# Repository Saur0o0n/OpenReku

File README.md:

<picture>
  <source media="(prefers-color-scheme: dark)" srcset=".github/images/openreku-logo-white.svg">
  
</picture>

Otwarty projekt sterownika rekuperatora opartego na ESP32 i ESPHome, współpracującego z Home Assistant. Obejmuje elektronikę sterownika oraz konfigurację obsługującą wentylatory, zawory i czujniki.

## Funkcje sterownika

OpenReku steruje wentylacją nawiewno-wywiewną i udostępnia nastawy oraz pomiary w Home Assistant. Regulacja wentylatorów, automatyka bypassu i procedura testowa działają lokalnie w ESPHome. Urządzenie ma też własny panel WWW i obsługuje aktualizacje przez Wi-Fi.

- **Regulacja dwóch wentylatorów** — niezależne ustawianie wydajności nawiewu i wywiewu albo praca zsynchronizowana. Tryb „Moc PWM” ustawia obu wentylatorom jednakowy procent wysterowania. Tryb „Przepływ powietrza” dostosowuje wywiew do zmierzonego przepływu nawiewu, dzięki czemu uwzględnia różnice oporów obu torów powietrza.
- **Korekta bilansu nawiew–wywiew** — w trybie synchronizacji przepływu można ustawić żądaną różnicę w m³/h. Dodatnia korekta oznacza przewagę nawiewu; regulator uzyskuje ją przez zmniejszenie wywiewu rekuperatora. Dołączona automatyzacja Home Assistant zmienia korektę podczas pracy wyciągu kuchennego.
- **Ręczny lub automatyczny bypass** — tryby „Automatyczne grzanie” i „Automatyczne chłodzenie” porównują temperaturę powietrza z czerpni z temperaturą wywiewaną z domu. Bypass otwiera się, gdy powietrze zewnętrzne sprzyja wybranemu celowi, a zamyka, gdy korzystniejszy jest odzysk ciepła lub chłodu. Histereza i czas potwierdzenia warunku ograniczają częste przełączanie.
- **Podgląd parametrów pracy** — temperatury i wilgotności w czterech punktach: czerpni, nawiewie, wywiewie i wyrzutni, a także obroty obu wentylatorów i przepływy powietrza, zależnie od wyposażenia. Zawartość wilgoci jest również obliczana w g/kg suchego powietrza. Karty Home Assistant udostępniają wykresy z zakładkami oraz wyliczaną po stronie HA sprawność temperaturową i odzysk wilgoci.
- **Test do obserwacji zużycia filtrów** — sterownik zamyka bypass, ustawia stałe wysterowanie wentylatorów i po ustabilizowaniu pracy uśrednia przepływ oraz obroty. Wyniki odniesione do nastawy PWM pozwalają porównywać kolejne pomiary; ostatni wynik jest zachowywany po restarcie. Na czas testu blokowane są zmiany nastaw, a po zakończeniu przywracane wcześniejsze ustawienia. Harmonogram zapewnia automatyzacja Home Assistant. Test dostarcza danych do oceny zmian, bez automatycznego alarmu wymiany filtra.

## Opis

Troche więcej o samym powstaniu projektu i co chciałem osiągnąć można przeczytać we [wpisie na mojej stronie](https://adrian.siemieniak.net/portal/sterownik-rekuperatora-cwk-450-o3zone-paruszewski/).

## Wyposażenie opcjonalne

Funkcje można dobrać do wyposażenia rekuperatora:

| Wariant / komponent | Dostępne funkcje |
| --- | --- |
| Dwa wentylatory ze sterowaniem PWM | Podstawowa regulacja niezależna lub wspólne wysterowanie w trybie „Moc PWM”, bez pomiaru przepływu. |
| Sygnały obrotów wentylatorów | Odczyt RPM i pomiary obrotów w procedurze testowej. Nie są wymagane do samego sterowania PWM. |
| Czujniki temperatury i wilgotności SHT4x | Monitoring do czterech torów powietrza. Temperatury czerpni i wywiewu służą automatyce bypassu, a nawiewu i wywiewu — obliczaniu przepływów. |
| Dwie zwężki Venturiego z czujnikami różnicy ciśnień SDP810-125Pa oraz pomiar temperatury nawiewu i wywiewu | Wyliczanie przepływów w m³/h, ich automatyczne bilansowanie i pomiary przepływu w teście filtrów. Obliczenia uwzględniają temperaturę powietrza oraz zadane wymiary zwężek. |
| Siłownik bypassu z osobnymi sygnałami otwierania i zamykania | Ręczne otwieranie i zamykanie, a z pomiarem temperatury czerpni i wywiewu także automatyczne grzanie lub chłodzenie. Czas ruchu jest ustawiany w konfiguracji; stan bypassu wynika z wydanych poleceń, bez pomiaru jego rzeczywistego położenia. |

Zamieszczony YAML odpowiada pełnemu zestawowi w instalacji autora. Warianty uproszczone wymagają dostosowania konfiguracji: usunięcia nieużywanych komponentów i zależnych od nich odczytów lub procedur. Nie ma automatycznego wykrywania wyposażenia ani gotowych profili tych wariantów.

## Zawartość repozytorium

| Katalog | Zawartość |
| --- | --- |
| [PCB/](PCB/) | Projekt płytki w wersji 1.1: schematy i PCB KiCad, lokalne biblioteki, lista elementów BOM, Gerbery do produkcji. |
| [ESPHome/](ESPHome/) | Konfiguracja `rekuperator.yaml` z obsługą urządzenia i integracją z Home Assistant oraz wzór `secrets.yaml.example` do uzupełnienia własnymi danymi dostępowymi. |
| [HomeAssistant/](HomeAssistant/) | Karta sterowania i wykresy Home Assistant, sensory sprawności, automatyzacje testu filtrów i korekty bilansu oraz podkład graficzny karty. |
| [Venturi/](Venturi/) | Model zwężki Venturiego do pomiaru przepływu powietrza: projekt FreeCAD i eksporty STEP obu części. |

Opis plików i instrukcję otwarcia projektu elektroniki zawiera [PCB/README.md](PCB/README.md). Przygotowanie konfiguracji i pliku sekretów opisano w [ESPHome/README.md](ESPHome/README.md). Sposób dodania karty do panelu opisano w [HomeAssistant/README.md](HomeAssistant/README.md).

## Licencja

Projekty PCB i mechaniki, dokumentacja i własne grafiki są udostępnione na licencji [CC BY-NC 4.0](LICENSES/CC-BY-NC-4.0.txt), a kod i konfiguracje YAML ESPHome oraz Home Assistant — na [PolyForm Noncommercial 1.0.0](LICENSES/PolyForm-Noncommercial-1.0.0.txt).

Możesz je kopiować, modyfikować i udostępniać do celów niekomercyjnych, na warunkach odpowiedniej licencji. Przy udostępnianiu zachowaj informację o autorze **Sauron**, nazwie **OpenReku**, [źródle projektu](https://github.com/Saur0o0n/OpenReku) i licencji; dla materiałów CC BY-NC oznacz również wprowadzone zmiany. Kod zawiera obowiązkową informację `Required Notice:`.

Zakres licencji i wyłączenia dotyczące cudzych materiałów określa [LICENSE](LICENSE). Wykorzystanie komercyjne wykraczające poza udzielone licencje wymaga osobnej zgody właścicieli praw.

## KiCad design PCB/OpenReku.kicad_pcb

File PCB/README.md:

# OpenReku — PCB 1.1

Projekt płytki sterownika rekuperatora OpenReku, rewizja **1.1 z 2026-10-01**. Ten katalog zawiera źródła KiCada, lokalne biblioteki, listę elementów i archiwum produkcyjne PCB. Oprogramowanie ESPHome i pozostałe komponenty projektu należą do osobnych katalogów repozytorium.

## Wizualizacja PCB

## Otwieranie projektu

Otwórz [OpenReku.kicad_pro](OpenReku.kicad_pro) w **KiCad 10**. Potrzebne są standardowe biblioteki symboli, footprintów i — do podglądu 3D — modeli KiCad 10.

Zachowaj razem wszystkie pliki z tego katalogu i podkatalog `Rekuperator.pretty`. KiCad odnajduje lokalne biblioteki względem katalogu, w którym znajduje się `OpenReku.kicad_pro`. Dzięki temu projekt można sklonować do dowolnego miejsca na komputerze.

Tabele `fp-lib-table` i `sym-lib-table` korzystają ze zmiennej `${KIPRJMOD}`, którą KiCad rozwija do katalogu projektu.

Lokalne biblioteki mają nazwę `Rekuperator`, używaną w odwołaniach schematu i PCB.

## Zawartość katalogu

| Plik lub katalog | Typ i przeznaczenie |
| --- | --- |
| [OpenReku.kicad_pro](OpenReku.kicad_pro) | Projekt KiCad: wspólne ustawienia schematu i PCB, klasy sieci oraz konfiguracja kontroli projektu. Główny plik do otwarcia. |
| [OpenReku.kicad_sch](OpenReku.kicad_sch) | Główny schemat KiCad: mikrokontroler, zasilanie części logicznej, interfejsy wentylatorów i odwołania do arkuszy podrzędnych. |
| [I2C.kicad_sch](I2C.kicad_sch) | Podrzędny arkusz schematu: multiplekser I²C i złącza czujników. Otwieraj w kontekście głównego projektu. |
| [230V.kicad_sch](230V.kicad_sch) | Podrzędny arkusz schematu: zasilanie sieciowe, zabezpieczenia, przekaźniki i wyjścia 230 V. |
| [OpenReku.kicad_pcb](OpenReku.kicad_pcb) | Projekt PCB KiCad: obrys płytki, rozmieszczenie elementów, ścieżki, przelotki, wylewki miedzi i nadruki. |
| [OpenReku.kicad_dru](OpenReku.kicad_dru) | Własne reguły DRC KiCada, w tym wymagane odstępy między częścią sieciową i niskonapięciową. |
| [Rekuperator.kicad_sym](Rekuperator.kicad_sym) | Lokalna biblioteka symboli schematowych KiCad; zawiera symbol przekaźnika SSR G3MB-202P. |
| [sym-lib-table](sym-lib-table) | Tabela bibliotek symboli projektu: rejestruje lokalną bibliotekę `Rekuperator.kicad_sym`. |
| [Rekuperator.pretty/](Rekuperator.pretty/) | Lokalna biblioteka footprintów KiCad. Każdy plik `.kicad_mod` opisuje pola lutownicze, obrysy lub grafikę jednego footprintu. Szczegóły poniżej. |
| [fp-lib-table](fp-lib-table) | Tabela bibliotek footprintów projektu: rejestruje katalog `Rekuperator.pretty`. |
| [BOM.csv](BOM.csv) | Lista elementów wersji 1.1, wyeksportowana z całej hierarchii schematu. Format CSV UTF-8, separator przecinek. |
| [OpenReku-v1.1-Gerber.zip](OpenReku-v1.1-Gerber.zip) | Archiwum do wykonania samej PCB: Gerbery obu warstw miedzi, obu soldermasek, górnego nadruku i obrysu, wiercenia PTH/NPTH oraz opis zadania `.gbrjob`. Nie zawiera plików automatycznego montażu. |

### Lokalna biblioteka footprintów

Poniższe pliki znajdują się w `Rekuperator.pretty/`:

| Plik `.kicad_mod` | Przeznaczenie |
| --- | --- |
| `ESP32-WROOM-32U_0.3mm_ThermalDrills.kicad_mod` | Footprint modułu ESP32-WROOM-32U z otworami termicznymi 0,3 mm. |
| `KLS2-EDV-5.08-04P-4_Vertical.kicad_mod` | Czteropinowe złącze interfejsu wentylatora, raster 5,08 mm. |
| `Omron_G3MB-202P_SIP4.kicad_mod` | Footprint przekaźnika SSR Omron G3MB-202P. |
| `PhoenixContact_MC_1,5_4-G-3.5_1x04_P3.50mm_Horizontal_Edge.kicad_mod` | Kątowe, czteropinowe złącze I²C, raster 3,50 mm, z obrysem dopasowanym do montażu przy krawędzi. |
| `PhoenixContact_MSTBA_2,5_2-G-5,08_1x02_P5.08mm_Horizontal_Edge.kicad_mod` | Kątowe, dwupinowe złącze 230 V, raster 5,08 mm, montowane przy krawędzi. |
| `PhoenixContact_MSTBA_2,5_3-G-5,08_1x03_P5.08mm_Horizontal_Edge.kicad_mod` | Kątowe, trzypinowe złącze 230 V, raster 5,08 mm, montowane przy krawędzi. |
| `Logo_OpenReku_36mm.kicad_mod` | Logo OR + OpenReku o szerokości 36 mm na górnej warstwie nadruku; nie jest elementem do zakupu. |

## BOM — lista elementów

`BOM.csv` zawiera **47 grup i 93 elementy**. Grupowanie uwzględnia wartość, footprint, numer części oraz pozostałe eksportowane właściwości, dzięki czemu elementy z odmiennymi uwagami montażowymi pozostają osobnymi pozycjami.

| Kolumna | Znaczenie |
| --- | --- |
| `Reference` | Oznaczenia elementów na schemacie i PCB, np. `R1,R2`. |
| `Quantity` | Liczba elementów w grupie. |
| `Value` | Wartość lub nazwa elementu ze schematu. |
| `Footprint` | Identyfikator biblioteki i footprintu KiCad. |
| `MPN` | Numer części producenta, jeżeli uzupełniono go w schemacie. |
| `MatingConnector` | Opis współpracującego wtyku; wtyk nie jest dodatkowo doliczony do `Quantity`. |
| `Pinout` | Opis wyprowadzeń zapisany w schemacie. |
| `AssemblyNote` | Uwagi montażowe, w tym warunki pominięcia rezystorów podciągających. |
| `DNP` | Oznaczenie elementu przewidzianego do pominięcia przy montażu, jeżeli ustawiono je w KiCadzie. |
| `Datasheet` | Odnośnik do dokumentacji części zapisany w schemacie. |

Puste pole oznacza brak informacji w schemacie. BOM nie obejmuje otworów montażowych H1–H4 ani logo LOGO1. Jest listą elementów projektu; współpracujące wtyki, przewody i osprzęt mechaniczny należy zestawić osobno.

Aby odtworzyć BOM, uruchom w tym katalogu:

```sh
kicad-cli sch export bom \
  --output BOM.csv \
  --fields 'Reference,QUANTITY,Value,Footprint,MPN,MatingConnector,Pinout,AssemblyNote,DNP,Datasheet' \
  --labels 'Reference,Quantity,Value,Footprint,MPN,MatingConnector,Pinout,AssemblyNote,DNP,Datasheet' \
  --group-by 'Value,Footprint,MPN,MatingConnector,Pinout,AssemblyNote,DNP,Datasheet' \
  --sort-field Reference \
  --ref-range-delimiter '' \
  OpenReku.kicad_sch
```

## Rewizja 1.1 względem 1.0

- Obrys PCB zmniejszono z 210 × 180 mm do **170 × 150 mm**.
- Rezystory R1–R41 i kondensatory ceramiczne C1/C3/C4/C5/C6/C7/C8 mają obudowy **1206**. C2 pozostaje tantalowy, a C9 przewlekany.
- Złącza I²C J4–J11 przesunięto o 2 mm w stronę krawędzi, zachowując raster 3,50 mm.
- Złącza 230 V J12–J17 zmieniono z rastra 7,62 mm na **5,08 mm**.
- Przeniesiono C5 i zarezerwowano miejsce dla dłuższego modułu ESP-32S 18 × 25,5 mm. Projekt elektryczny nadal wskazuje ESP32-WROOM-32U; zgodność innego modułu wymaga sprawdzenia jego padów i sposobu podłączenia anteny.
- Zmieniono rozmieszczenie i routing oraz dodano logo OR + OpenReku na górnym nadruku.

Źródła i Gerbery wersji **1.0** są dostępne w historii Git, w commicie `764cad7`. Bieżący katalog zawiera rewizję **1.1**.

## Produkcja PCB

Pliki do wykonania płytki znajdują się w [OpenReku-v1.1-Gerber.zip](OpenReku-v1.1-Gerber.zip). Parametry zamówienia:

- wymiary: **170 × 150 mm**;
- **2 warstwy**, laminat **FR-4 1,6 mm**;
- miedź **35 µm / 1 oz**;
- soldermaska obustronna, nadruk na górze.

Po zmianie projektu PCB należy ponownie wygenerować Gerbery i pliki wierceń.

Reguły DRC określają odstępy 8 mm między częścią sieciową i niskonapięciową oraz 3 mm między różnymi sieciami części sieciowej.

Pliki lokalnych ustawień `*.kicad_prl`, blokady `*.lck`, autosave, kopie zapasowe i cache footprintów są pomijane przez główny [`.gitignore`](../.gitignore). Nie są potrzebne do odtworzenia projektu.

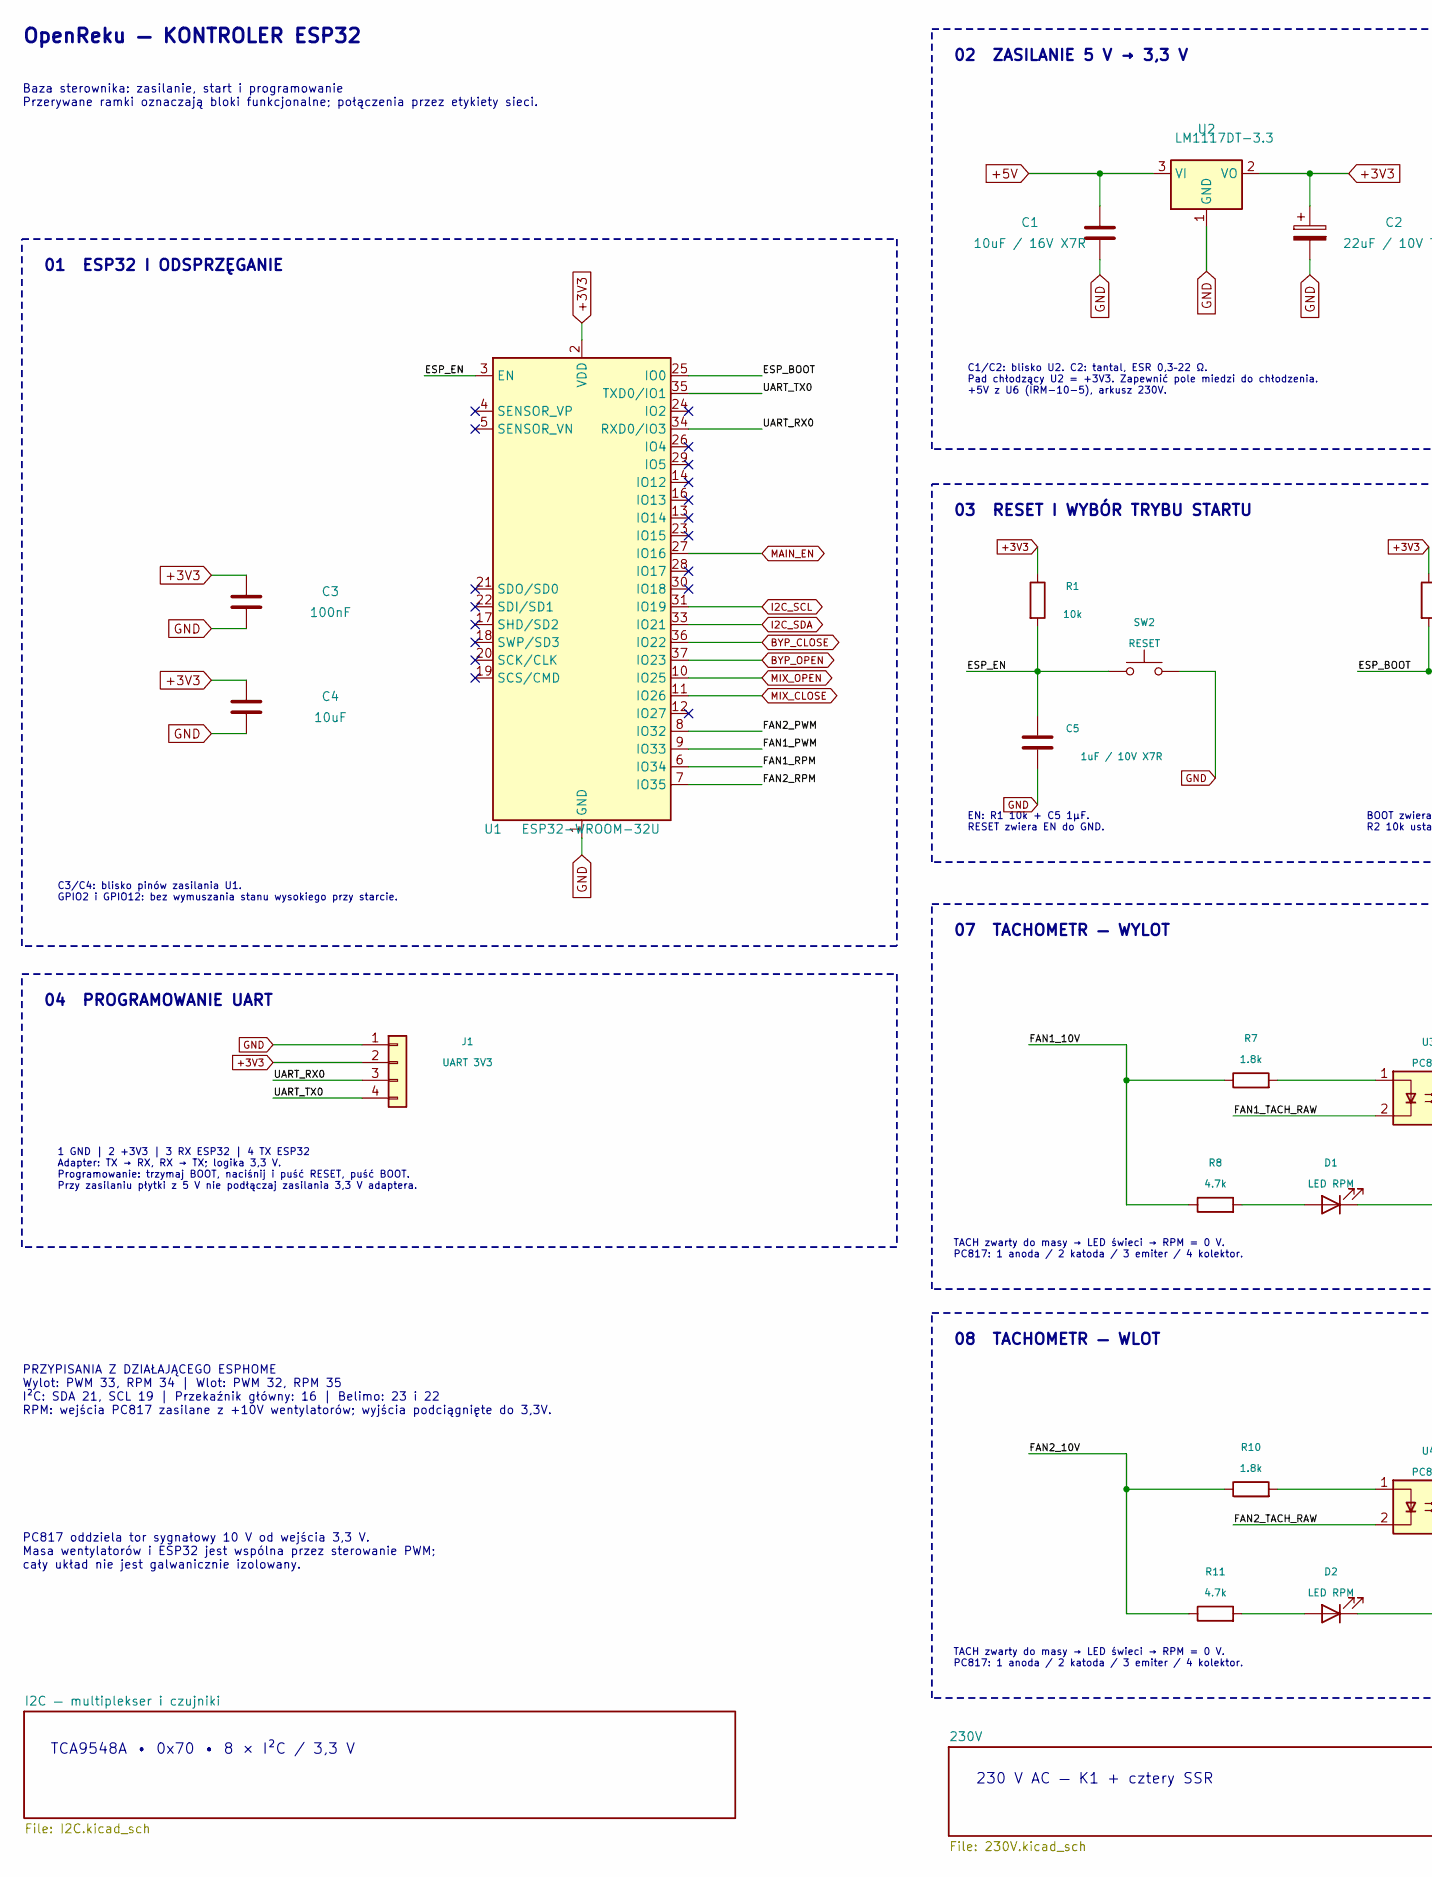
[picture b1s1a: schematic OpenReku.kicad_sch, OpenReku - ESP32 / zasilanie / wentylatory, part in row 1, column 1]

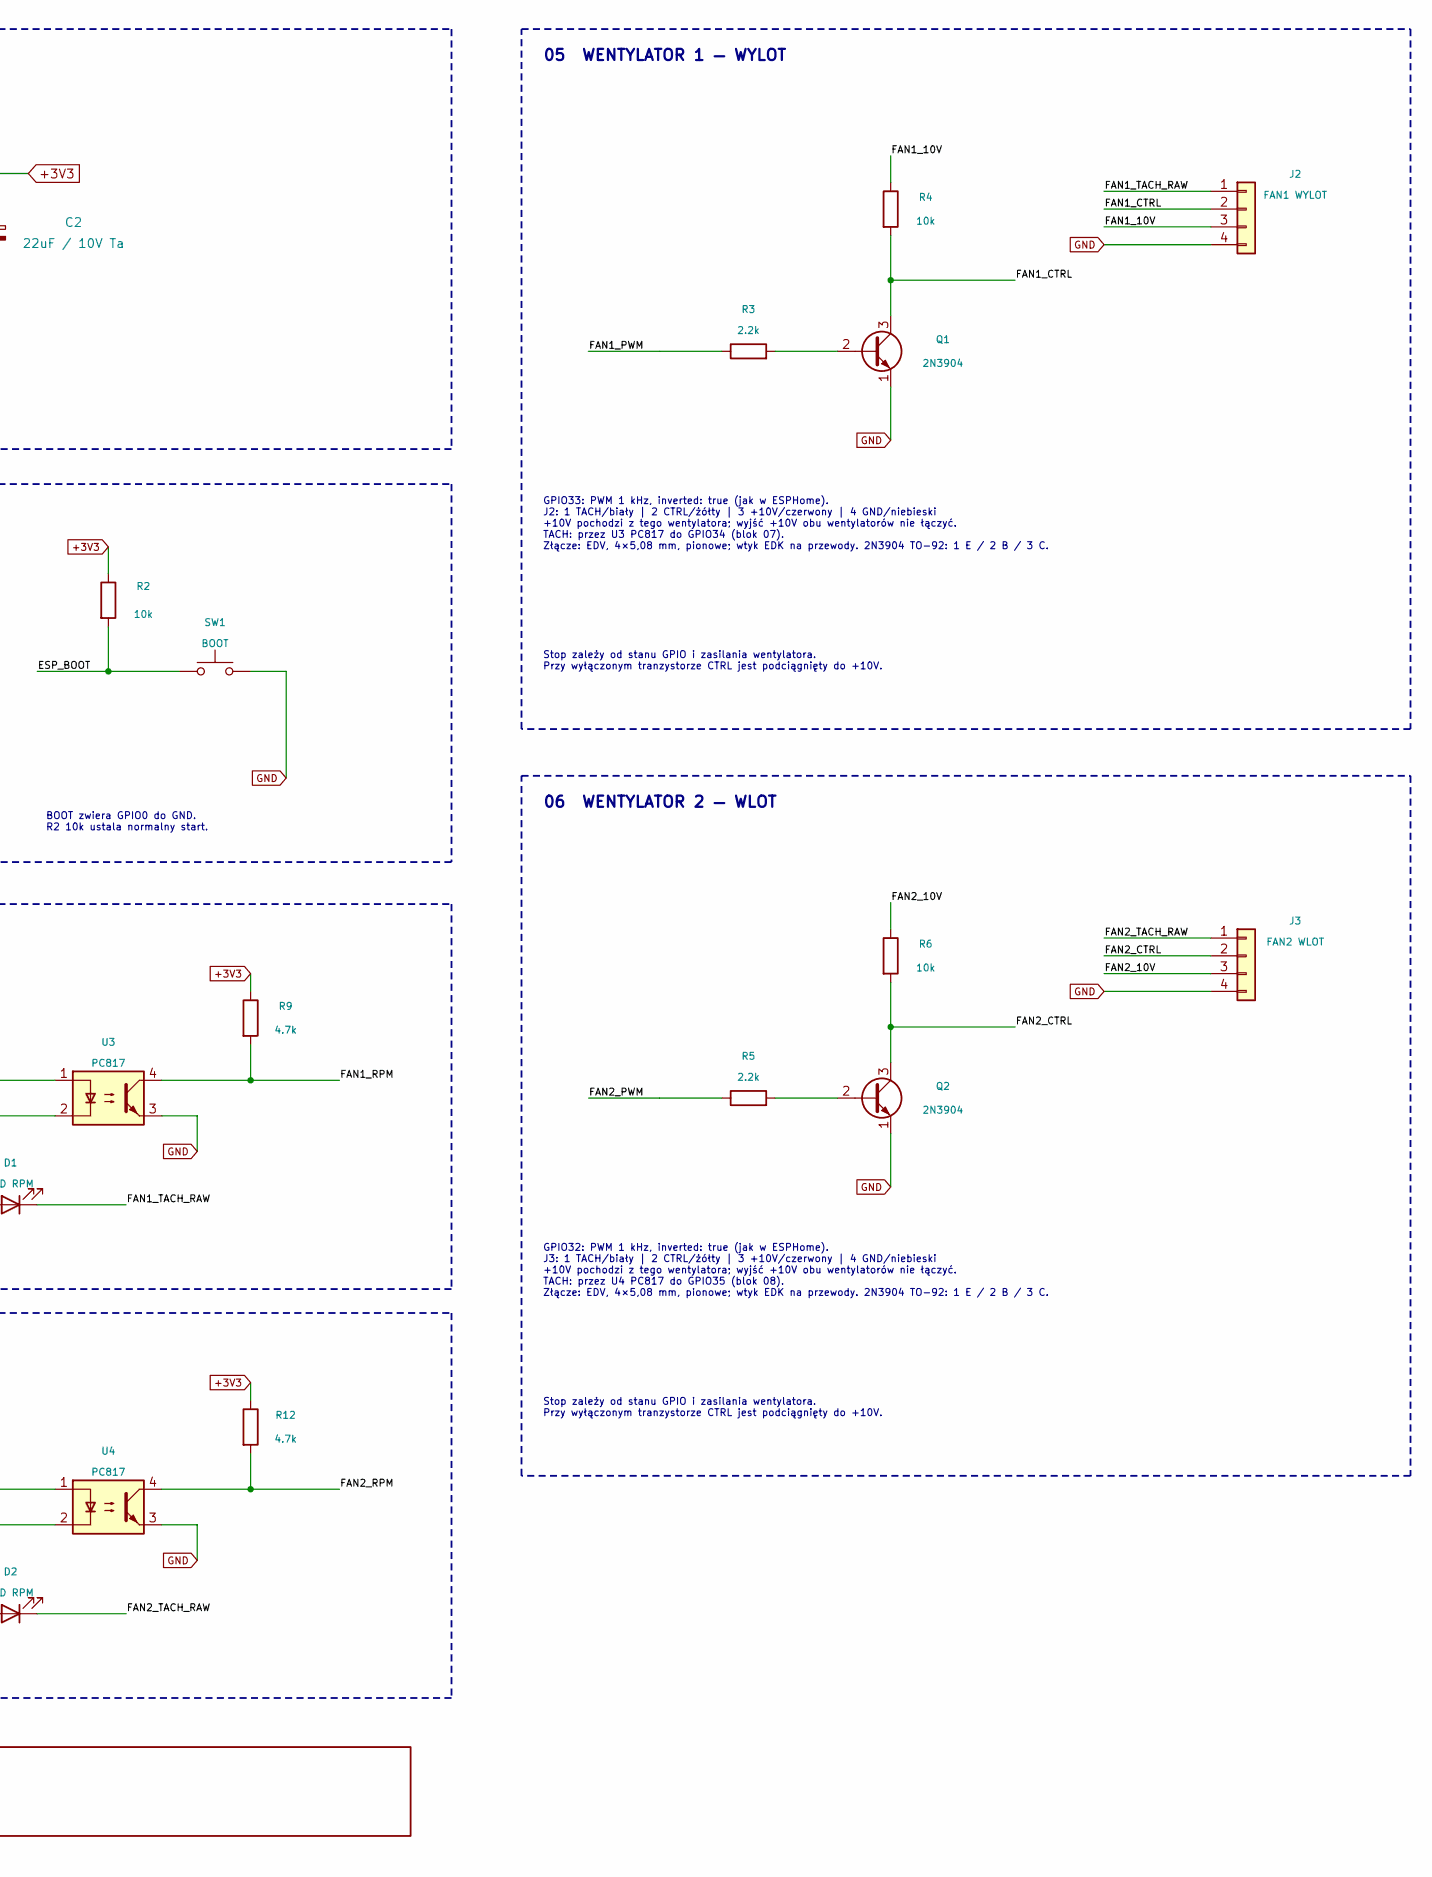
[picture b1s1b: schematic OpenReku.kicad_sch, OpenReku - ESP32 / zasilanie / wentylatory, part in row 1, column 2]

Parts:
C1: 10uF / 16V X7R; C_1206_3216Metric
C2: 22uF / 10V Ta; CP_EIA-3528-21_Kemet-B
C3: 100nF; C_1206_3216Metric
C4: 10uF; C_1206_3216Metric
C5: 1uF / 10V X7R; C_1206_3216Metric
D1, D2: LED RPM; LED_D3.0mm
J1: UART 3V3; PinHeader_1x04_P2.54mm_Vertical
J2: FAN1 WYLOT; KLS2-EDV-5.08-04P-4_Vertical; MPN KLS2-EDV-5.08-04P-4
J3: FAN2 WLOT; KLS2-EDV-5.08-04P-4_Vertical; MPN KLS2-EDV-5.08-04P-4
Q1, Q2: 2N3904; TO-92_Inline
R1, R2, R4, R6: 10k; R_1206_3216Metric
R3, R5: 2.2k; R_1206_3216Metric
R7, R10: 1.8k; R_1206_3216Metric
R8, R9, R11, R12: 4.7k; R_1206_3216Metric
SW1: BOOT; SW_PUSH_6mm
SW2: RESET; SW_PUSH_6mm
U1: ESP32-WROOM-32U; ESP32-WROOM-32U_0.3mm_ThermalDrills
U2: LM1117DT-3.3; TO-252-3_TabPin2
U3, U4: PC817; DIP-4_W7.62mm

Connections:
+3V3: C2.1, C3.1, C4.1, J1.2, R1.1, R2.1, R9.1, R12.1, U1.2 (VDD), U2.2 (VO); also elsewhere on the board
+5V: C1.1, U2.3 (VI); also elsewhere on the board
/ESP_BOOT: R2.2, SW1.1, U1.25 (IO0)
/ESP_EN: C5.1, R1.2, SW2.1, U1.3 (EN)
/FAN1_10V: J2.3, R4.1, R7.1, R8.1
/FAN1_CTRL: J2.2, Q1.3 (C), R4.2
/FAN1_PWM: R3.1, U1.9 (IO33)
/FAN1_RPM: R9.2, U1.6 (IO34), U3.4
/FAN1_TACH_RAW: D1.1 (K), J2.1, U3.2
/FAN2_10V: J3.3, R6.1, R10.1, R11.1
/FAN2_CTRL: J3.2, Q2.3 (C), R6.2
/FAN2_PWM: R5.1, U1.8 (IO32)
/FAN2_RPM: R12.2, U1.7 (IO35), U4.4
/FAN2_TACH_RAW: D2.1 (K), J3.1, U4.2
/UART_RX0: J1.3, U1.34 (RXD0/IO3)
/UART_TX0: J1.4, U1.35 (TXD0/IO1)
BYP_CLOSE: U1.36 (IO22); also elsewhere on the board
BYP_OPEN: U1.37 (IO23); also elsewhere on the board
GND: C1.2, C2.2, C3.2, C4.2, C5.2, J1.1, J2.4, J3.4, Q1.1 (E), Q2.1 (E), SW1.2, SW2.2, U1.1 (GND), U1.15 (GND), U1.38 (GND), U1.39 (GND), U2.1 (GND), U3.3, U4.3; also elsewhere on the board
I2C_SCL: U1.31 (IO19); also elsewhere on the board
I2C_SDA: U1.33 (IO21); also elsewhere on the board
MAIN_EN: U1.27 (IO16); also elsewhere on the board
MIX_CLOSE: U1.11 (IO26); also elsewhere on the board
MIX_OPEN: U1.10 (IO25); also elsewhere on the board
unnamed: D1.2 (A), R8.2
unnamed: D2.2 (A), R11.2
unnamed: Q1.2 (B), R3.2
unnamed: Q2.2 (B), R5.2
unnamed: R7.2, U3.1
unnamed: R10.2, U4.1

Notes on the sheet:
01 ESP32 I ODSPRZĘGANIE
02 ZASILANIE 5 V → 3,3 V
03 RESET I WYBÓR TRYBU STARTU
04 PROGRAMOWANIE UART
C3/C4: blisko pinów zasilania U1. GPIO2 i GPIO12: bez wymuszania stanu wysokiego przy starcie.
C1/C2: blisko U2. C2: tantal, ESR 0,3–22 Ω. Pad chłodzący U2 = +3V3. Zapewnić pole miedzi do chłodzenia. +5V z U6 (IRM-10-5), arkusz 230V.
EN: R1 10k + C5 1µF. RESET zwiera EN do GND.
BOOT zwiera GPIO0 do GND. R2 10k ustala normalny start.
1 GND | 2 +3V3 | 3 RX ESP32 | 4 TX ESP32 Adapter: TX → RX, RX → TX; logika 3,3 V. Programowanie: trzymaj BOOT, naciśnij i puść RESET, puść BOOT. Przy zasilaniu płytki z 5 V nie podłączaj zasilania 3,3 V adaptera.
OpenReku — KONTROLER ESP32
Baza sterownika: zasilanie, start i programowanie Przerywane ramki oznaczają bloki funkcjonalne; połączenia przez etykiety sieci.
05 WENTYLATOR 1 — WYLOT
GPIO33: PWM 1 kHz, inverted: true (jak w ESPHome). J2: 1 TACH/biały | 2 CTRL/żółty | 3 +10V/czerwony | 4 GND/niebieski +10V pochodzi z tego wentylatora; wyjść +10V obu wentylatorów nie łączyć. TACH: przez U3 PC817 do GPIO34 (blok 07). Złącze: EDV, 4×5,08 mm, pionowe; wtyk EDK na przewody. 2N3904 TO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
Stop zależy od stanu GPIO i zasilania wentylatora. Przy wyłączonym tranzystorze CTRL jest podciągnięty do +10V.
06 WENTYLATOR 2 — WLOT
GPIO32: PWM 1 kHz, inverted: true (jak w ESPHome). J3: 1 TACH/biały | 2 CTRL/żółty | 3 +10V/czerwony | 4 GND/niebieski +10V pochodzi z tego wentylatora; wyjść +10V obu wentylatorów nie łączyć. TACH: przez U4 PC817 do GPIO35 (blok 08). Złącze: EDV, 4×5,08 mm, pionowe; wtyk EDK na przewody. 2N3904 TO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
PRZYPISANIA Z DZIAŁAJĄCEGO ESPHOME Wylot: PWM 33, RPM 34 | Wlot: PWM 32, RPM 35 I²C: SDA 21, SCL 19 | Przekaźnik główny: 16 | Belimo: 23 i 22 RPM: wejścia PC817 zasilane z +10V wentylatorów; wyjścia podciągnięte do 3,3V.
07 TACHOMETR — WYLOT
TACH zwarty do masy → LED świeci → RPM = 0 V. PC817: 1 anoda / 2 katoda / 3 emiter / 4 kolektor.
08 TACHOMETR — WLOT
PC817 oddziela tor sygnałowy 10 V od wejścia 3,3 V. Masa wentylatorów i ESP32 jest wspólna przez sterowanie PWM; cały układ nie jest galwanicznie izolowany.
TCA9548A • 0x70 • 8 × I²C / 3,3 V
230 V AC — K1 + cztery SSR

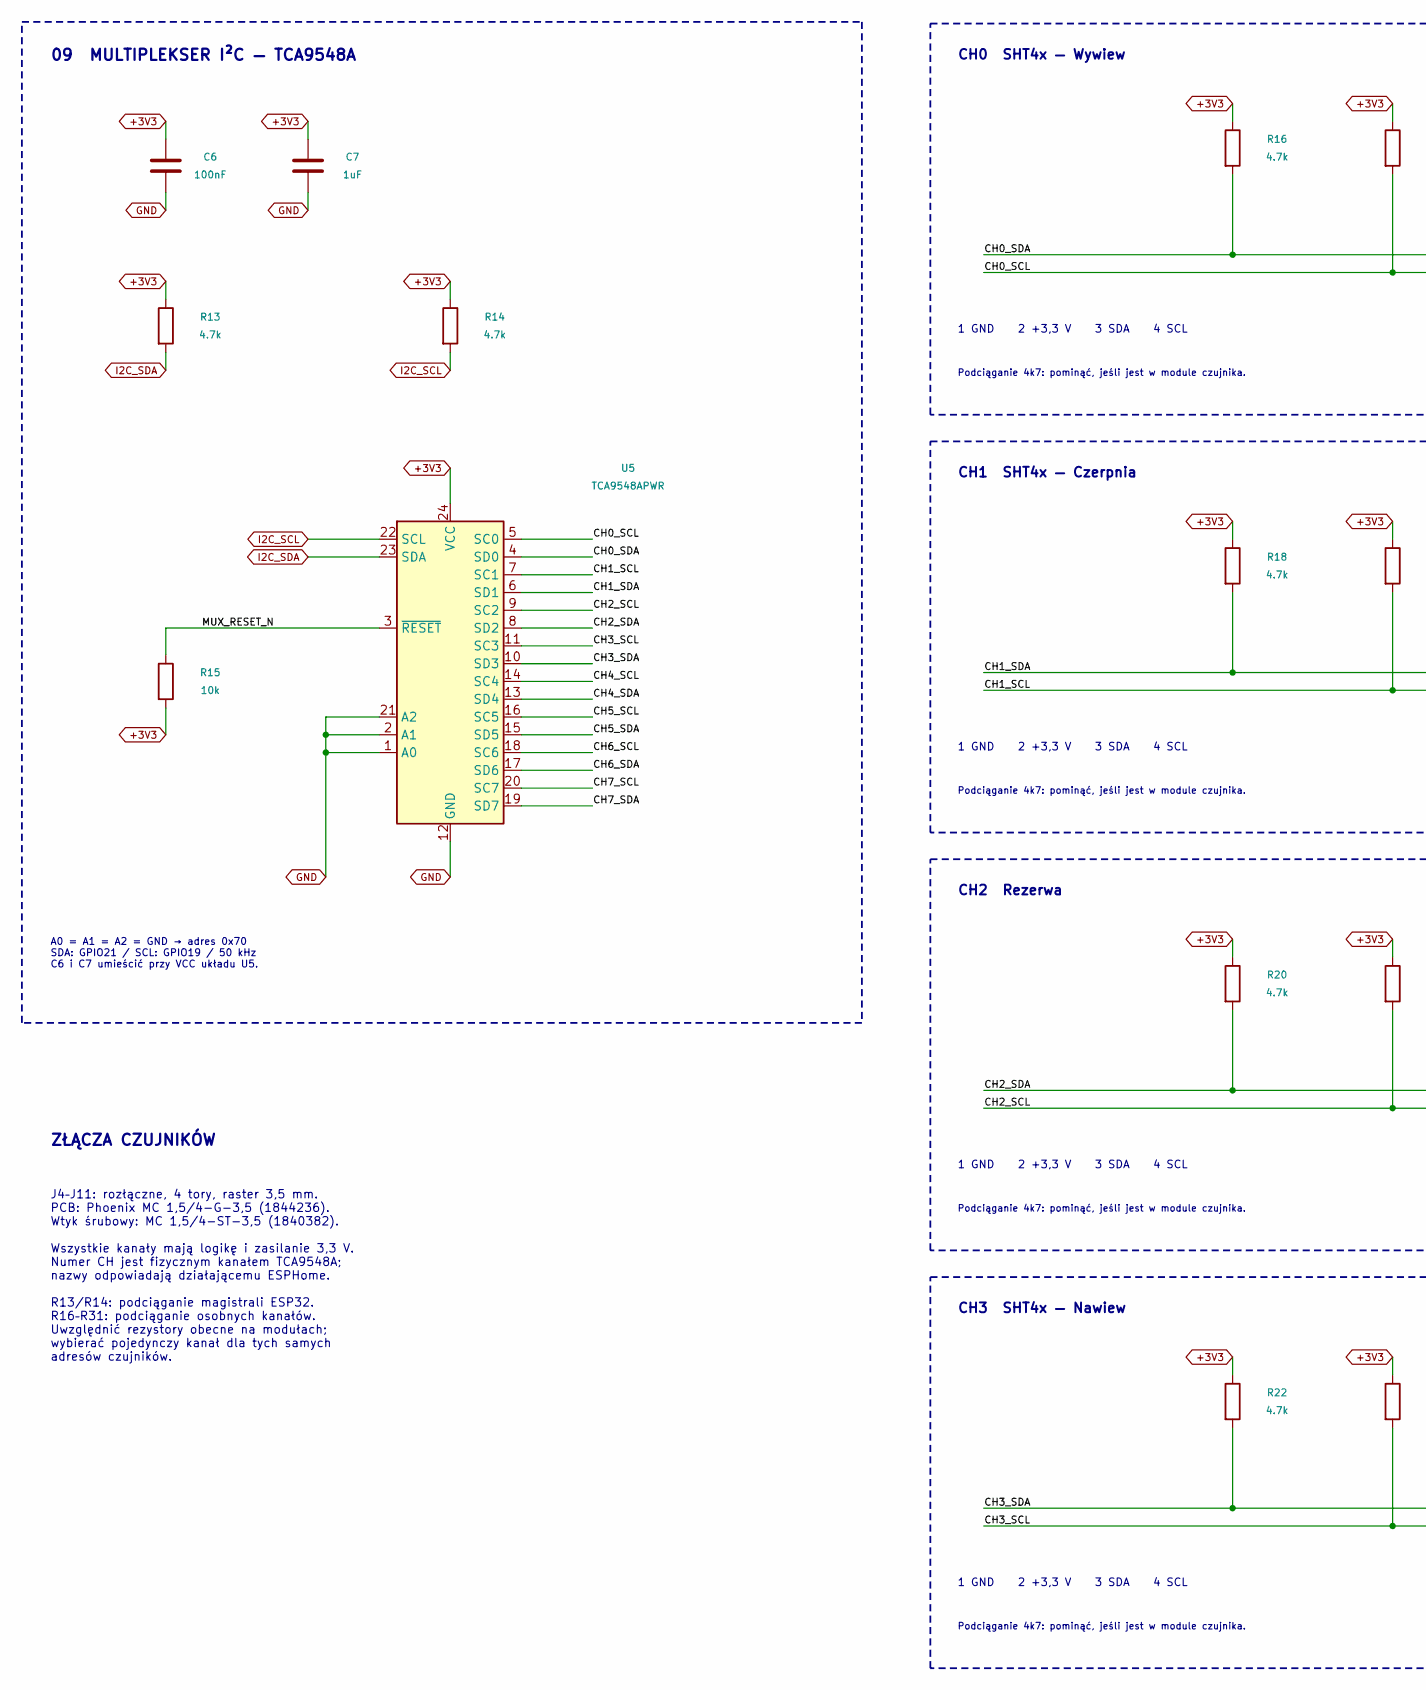
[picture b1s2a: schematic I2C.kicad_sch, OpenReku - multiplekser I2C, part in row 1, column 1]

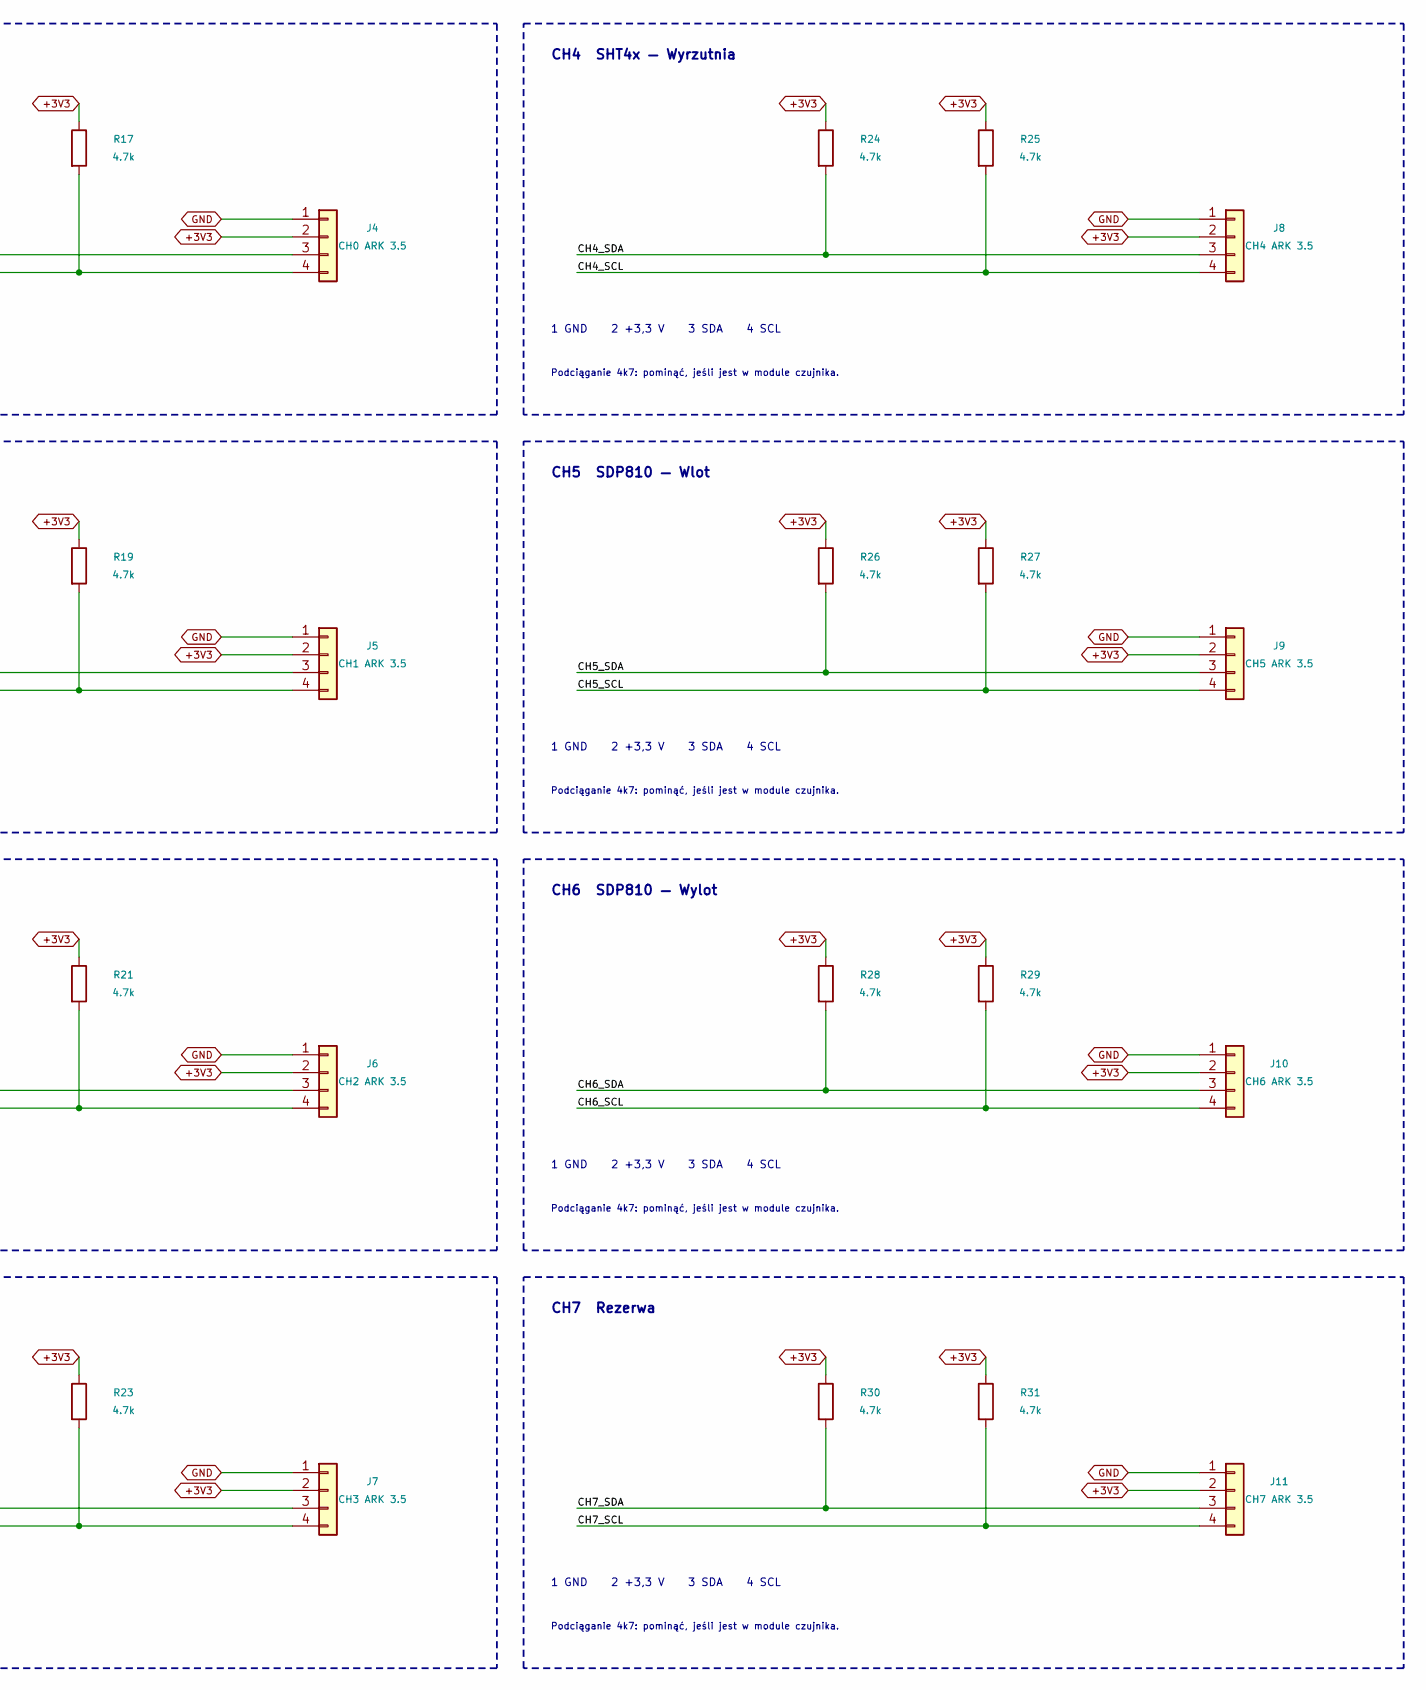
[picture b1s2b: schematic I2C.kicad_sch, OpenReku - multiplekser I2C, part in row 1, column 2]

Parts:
C6: 100nF; C_1206_3216Metric
C7: 1uF; C_1206_3216Metric
J4: CH0 ARK 3.5; PhoenixContact_MC_1,5_4-G-3.5_1x04_P3.50mm_Horizontal_Edge; MPN 1844236
J5: CH1 ARK 3.5; PhoenixContact_MC_1,5_4-G-3.5_1x04_P3.50mm_Horizontal_Edge; MPN 1844236
J6: CH2 ARK 3.5; PhoenixContact_MC_1,5_4-G-3.5_1x04_P3.50mm_Horizontal_Edge; MPN 1844236
J7: CH3 ARK 3.5; PhoenixContact_MC_1,5_4-G-3.5_1x04_P3.50mm_Horizontal_Edge; MPN 1844236
J8: CH4 ARK 3.5; PhoenixContact_MC_1,5_4-G-3.5_1x04_P3.50mm_Horizontal_Edge; MPN 1844236
J9: CH5 ARK 3.5; PhoenixContact_MC_1,5_4-G-3.5_1x04_P3.50mm_Horizontal_Edge; MPN 1844236
J10: CH6 ARK 3.5; PhoenixContact_MC_1,5_4-G-3.5_1x04_P3.50mm_Horizontal_Edge; MPN 1844236
J11: CH7 ARK 3.5; PhoenixContact_MC_1,5_4-G-3.5_1x04_P3.50mm_Horizontal_Edge; MPN 1844236
R13, R14, R16, R17, R18, R19, R20, R21, R22, R23, R24, R25, R26, R27, R28, R29, R30, R31: 4.7k; R_1206_3216Metric
R15: 10k; R_1206_3216Metric
U5: TCA9548APWR; TSSOP-24_4.4x7.8mm_P0.65mm; MPN TCA9548APWR

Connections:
+3V3: C6.1, C7.1, J4.2, J5.2, J6.2, J7.2, J8.2, J9.2, J10.2, J11.2, R13.1, R14.1, R15.2, R16.1, R17.1, R18.1, R19.1, R20.1, R21.1, R22.1, R23.1, R24.1, R25.1, R26.1, R27.1, R28.1, R29.1, R30.1, R31.1, U5.24 (VCC); also elsewhere on the board
/I2C — multiplekser i czujniki/CH0_SCL: J4.4, R17.2, U5.5 (SC0)
/I2C — multiplekser i czujniki/CH0_SDA: J4.3, R16.2, U5.4 (SD0)
/I2C — multiplekser i czujniki/CH1_SCL: J5.4, R19.2, U5.7 (SC1)
/I2C — multiplekser i czujniki/CH1_SDA: J5.3, R18.2, U5.6 (SD1)
/I2C — multiplekser i czujniki/CH2_SCL: J6.4, R21.2, U5.9 (SC2)
/I2C — multiplekser i czujniki/CH2_SDA: J6.3, R20.2, U5.8 (SD2)
/I2C — multiplekser i czujniki/CH3_SCL: J7.4, R23.2, U5.11 (SC3)
/I2C — multiplekser i czujniki/CH3_SDA: J7.3, R22.2, U5.10 (SD3)
/I2C — multiplekser i czujniki/CH4_SCL: J8.4, R25.2, U5.14 (SC4)
/I2C — multiplekser i czujniki/CH4_SDA: J8.3, R24.2, U5.13 (SD4)
/I2C — multiplekser i czujniki/CH5_SCL: J9.4, R27.2, U5.16 (SC5)
/I2C — multiplekser i czujniki/CH5_SDA: J9.3, R26.2, U5.15 (SD5)
/I2C — multiplekser i czujniki/CH6_SCL: J10.4, R29.2, U5.18 (SC6)
/I2C — multiplekser i czujniki/CH6_SDA: J10.3, R28.2, U5.17 (SD6)
/I2C — multiplekser i czujniki/CH7_SCL: J11.4, R31.2, U5.20 (SC7)
/I2C — multiplekser i czujniki/CH7_SDA: J11.3, R30.2, U5.19 (SD7)
/I2C — multiplekser i czujniki/MUX_RESET_N: R15.1, U5.3 (~RESET)
GND: C6.2, C7.2, J4.1, J5.1, J6.1, J7.1, J8.1, J9.1, J10.1, J11.1, U5.1 (A0), U5.2 (A1), U5.12 (GND), U5.21 (A2); also elsewhere on the board
I2C_SCL: R14.2, U5.22 (SCL); also elsewhere on the board
I2C_SDA: R13.2, U5.23 (SDA); also elsewhere on the board

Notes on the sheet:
09 MULTIPLEKSER I²C — TCA9548A
A0 = A1 = A2 = GND → adres 0x70 SDA: GPIO21 / SCL: GPIO19 / 50 kHz C6 i C7 umieścić przy VCC układu U5.
CH0 SHT4x — Wywiew
1 GND 2 +3,3 V 3 SDA 4 SCL
Podciąganie 4k7: pominąć, jeśli jest w module czujnika.
CH1 SHT4x — Czerpnia
CH2 Rezerwa
CH3 SHT4x — Nawiew
CH4 SHT4x — Wyrzutnia
CH5 SDP810 — Wlot
CH6 SDP810 — Wylot
CH7 Rezerwa
ZŁĄCZA CZUJNIKÓW
J4–J11: rozłączne, 4 tory, raster 3,5 mm. PCB: Phoenix MC 1,5/4-G-3,5 (1844236). Wtyk śrubowy: MC 1,5/4-ST-3,5 (1840382). Wszystkie kanały mają logikę i zasilanie 3,3 V. Numer CH jest fizycznym kanałem TCA9548A; nazwy odpowiadają działającemu ESPHome. R13/R14: podciąganie magistrali ESP32. R16–R31: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
